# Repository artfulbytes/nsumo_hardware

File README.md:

# Nsumo hardware
This repository contains the schematic and PCB design of Nsumo, a mini-class Sumobot (500g 10x10cm),
created in KiCad, and manufactured by JLCPCB. It's a 2-layer PCB with microcontroller MSP430G2553IPW28,
regulators 3.3V (AMS1117-3.3) and 5V (MP2359), two motor drivers TB6612FNG, IR receiver TSP382, and
circuit protection (RS3E075AT).

## Setup
Import the project into KiCad >6.0 and make sure you have the "default global symbol library table"
and the "default footprint library" available. KiCad should find the 3Dmodels and symbols under _libs/_
automatically. You must manually import the footprints under _libs/footprints/_ (select "file/add library"
from the menu in the footprint editor and add them to the project).

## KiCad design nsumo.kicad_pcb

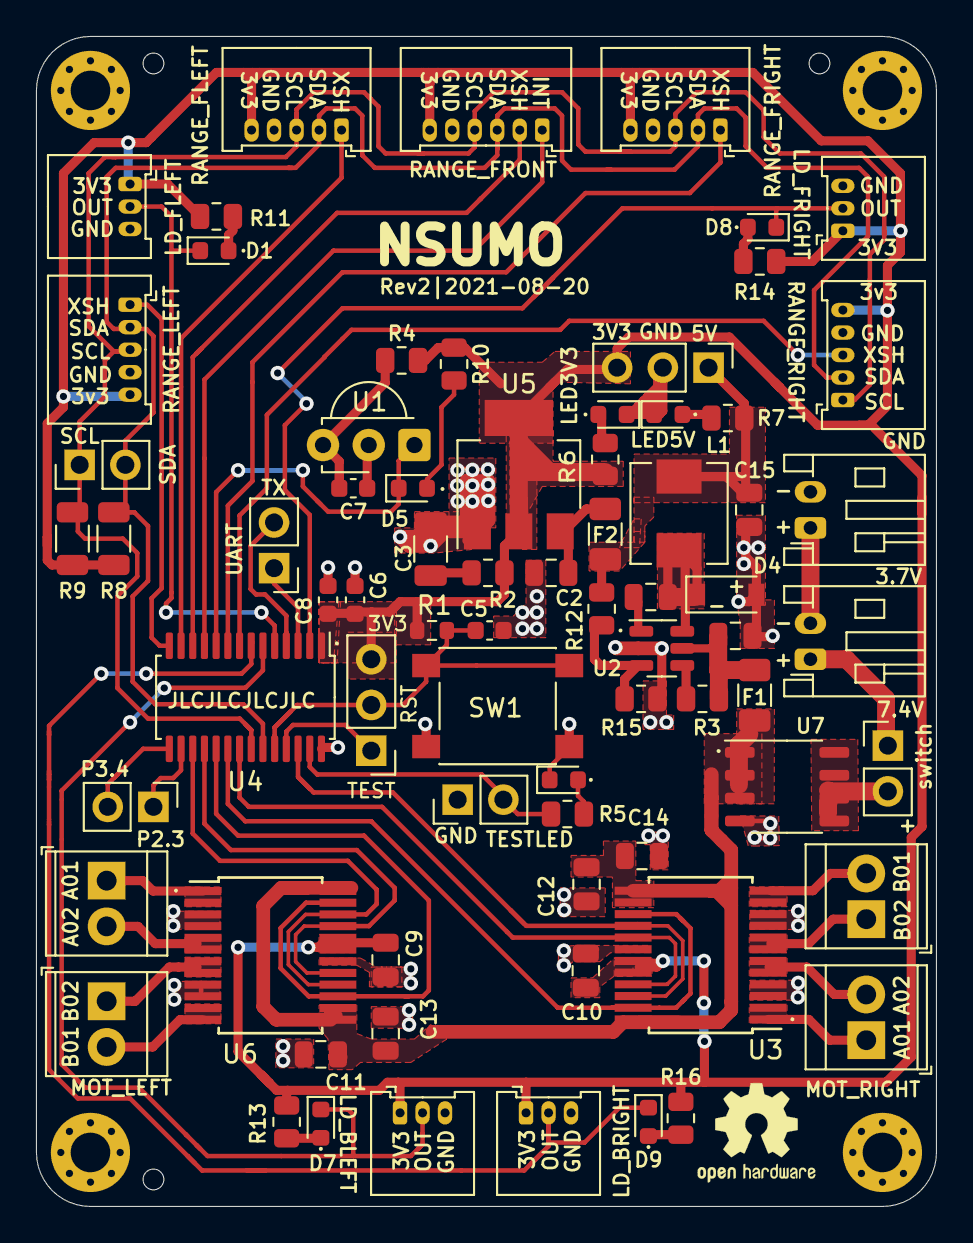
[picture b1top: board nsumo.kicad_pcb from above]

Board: 2 copper layers, 50.0 x 65.0 mm, 77 parts (0 on the bottom side), 57 nets.

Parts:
C1, C13, C14: 10uF; C_0805_2012Metric
C2: 1uF; C_0805_2012Metric
C3: 47uF; C_1206_3216Metric
C4: 10nF; C_0805_2012Metric
C5: 1nF; C_0603_1608Metric
C6: 10uF; C_0603_1608Metric
C7: 1uF; C_0603_1608Metric
C8: 100nF; C_0603_1608Metric
C9, C10, C11, C12: 0.1uF; C_0805_2012Metric
C15: 22uF; C_0805_2012Metric
D1, D5, D7, D8, D9: RED; LED_0603_1608Metric
D2: GREEN; LED_0603_1608Metric
D3: YELLOW; LED_0603_1608Metric
D4: B5819W; D_SOD-123
D6: BLUE; LED_0603_1608Metric
F1, F2: 750mA; Fuse_1206_3216Metric
H1, H2, H3, H4: MountingHole_Pad; MountingHole_2.2mm_M2_Pad_Via
J1: Range_sensor_left; Molex_PicoBlade_53048-0510_1x05_P1.25mm_Horizontal
J2: Range_sensor_front; Molex_PicoBlade_53048-0610_1x06_P1.25mm_Horizontal
J3: BattConn1; JST_PH_S2B-PH-K_1x02_P2.00mm_Horizontal
J4: Range_sensor_front_left; Molex_PicoBlade_53048-0510_1x05_P1.25mm_Horizontal
J5: BattConn0; JST_PH_S2B-PH-K_1x02_P2.00mm_Horizontal
J6: I2C; PinHeader_1x02_P2.54mm_Vertical
J7: Range_sensor_front_right; Molex_PicoBlade_53048-0510_1x05_P1.25mm_Horizontal
J8: UNUSED; PinHeader_1x02_P2.54mm_Vertical
J9: Range_sensor_right; Molex_PicoBlade_53048-0510_1x05_P1.25mm_Horizontal
J10: UART; PinHeader_1x02_P2.54mm_Vertical
J11: SWD; PinHeader_1x03_P2.54mm_Vertical
J12: LED; PinHeader_1x02_P2.54mm_Vertical
J13: PWR; PinHeader_1x03_P2.54mm_Vertical
J14: MOT_FRONT_RIGHT; TerminalBlock_TE_282834-2_1x02_P2.54mm_Horizont
J15: MOT_BACK_RIGHT; TerminalBlock_TE_282834-2_1x02_P2.54mm_Horizont
J16: MOT_FRONT_LEFT; TerminalBlock_TE_282834-2_1x02_P2.54mm_Horizont
J17: MOT_BACK_LEFT; TerminalBlock_TE_282834-2_1x02_P2.54mm_Horizont
J19: Ld_front_left; Molex_PicoBlade_53048-0310_1x03_P1.25mm_Horizontal
J20: Ld_back_left; Molex_PicoBlade_53048-0310_1x03_P1.25mm_Horizontal
J21: Ld_front_right; Molex_PicoBlade_53048-0310_1x03_P1.25mm_Horizontal
J22: Ld_back_right; Molex_PicoBlade_53048-0310_1x03_P1.25mm_Horizontal
L1: 10uH; L_Sunlord_MWSA0518_5.4x5.2mm
R1: 47k; R_0603_1608Metric
R2: 1; R_0805_2012Metric
R3: 100k; R_0805_2012Metric
R4, R5: 470; R_0805_2012Metric
R6, R7: 1k; R_0805_2012Metric
R8, R9: 10k; R_1206_3216Metric
R10, R11, R13, R14, R16: 100; R_0805_2012Metric
R12: 49.9k; R_0805_2012Metric
R15: 9.53k; R_0805_2012Metric
SW1: SW_DPST_x2; SW_Push_1P1T_NO_6x6mm_H9.5mm
SW2: SW_SPST; PinHeader_1x02_P2.54mm_Vertical
U1: TSOP382xx; Vishay_MINICAST-3Pin
U2: MP2359; TSOT-23-6
U3, U6: TB6612FNG; SSOP-24_5.3x8.2mm_P0.65mm_LongPads
U4: MSP430G2553IPW28; TSSOP-28_4.4x9.7mm_P0.65mm
U5: AMS1117-3.3; SOT-223-3_TabPin2
U7: RS3E075AT; SOP-8_3.9x4.9mm_P1.27mm

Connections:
+3V3: C6.1, C8.1, C9.1, C10.1, J1.5, J2.6, J4.5, J7.5, J9.5, J11.3, J13.3, J19.1, J20.1, J21.1, J22.1, R1.2, R2.1, R4.2, R6.1, R8.1, R9.1, R10.1, R11.1, R13.1, R14.1, R16.1, U3.19, U3.20, U4.1, U5.2, U6.19, U6.20
+5V: C15.1, F2.1, J13.1, L1.2, R7.1, R12.1
+BATT: C11.1, C12.1, C13.1, C14.1, F1.1, U3.13, U3.14, U3.24, U6.13, U6.14, U6.24, U7.1, U7.2, U7.3
GND: C1.2, C2.2, C3.2, C5.2, C6.2, C7.2, C8.2, C9.2, C10.2, C11.2, C12.2, C13.2, C14.2, C15.2, D2.1, D3.1, D4.2, D6.1, H1.1, H2.1, H3.1, H4.1, J1.4, J2.5, J4.4, J5.2, J7.4, J9.4, J12.1, J13.2, J19.3, J20.3, J21.3, J22.3, R15.2, SW1.1, U1.2, U2.2, U3.3, U3.4, U3.9, U3.10, U3.18, U4.28, U5.1, U6.3, U6.4, U6.9, U6.10, U6.18, U7.4
INT_FRONT: J2.1, U4.11
IR_RECEIVER: D5.1, U1.1, U4.10
LD_BACK_LEFT: D7.1, J20.2, U4.6
LD_BACK_RIGHT: D9.1, J22.2, U4.7
LD_FRONT_LEFT: D1.1, J19.2, U4.5
LD_FRONT_RIGHT: D8.1, J21.2, U4.2
ML_A01: J17.1, U6.1, U6.2
ML_A02: J17.2, U6.5, U6.6
ML_B01: J16.2, U6.11, U6.12
ML_B02: J16.1, U6.7, U6.8
MOTS_LEFT_CH1: U4.18, U6.17, U6.21
MOTS_LEFT_CH2: U4.17, U6.16, U6.22
MOTS_LEFT_PWM: U4.19, U6.15, U6.23
MOTS_RIGHT_CH1: U3.17, U3.21, U4.21
MOTS_RIGHT_CH2: U3.16, U3.22, U4.26
MOTS_RIGHT_PWM: U3.15, U3.23, U4.20
MR_A01: J15.1, U3.1, U3.2
MR_A02: J15.2, U3.5, U3.6
MR_B01: J14.2, U3.11, U3.12
MR_B02: J14.1, U3.7, U3.8
unnamed: C1.1, F1.2, R3.1, U2.5
unnamed: C2.1, F2.2, U5.3
unnamed: C3.1, R2.2
unnamed: C4.1, U2.1
unnamed: C4.2, D4.1, L1.1, U2.6
unnamed: C7.1, R4.1, U1.3
unnamed: D1.2, R11.2
unnamed: D2.2, R6.2
unnamed: D3.2, R7.2
unnamed: D5.2, R10.2
unnamed: D6.2, R5.2
unnamed: D7.2, R13.2
unnamed: D8.2, R14.2
unnamed: D9.2, R16.2
unnamed: J3.1, SW2.1
unnamed: J3.2, J5.1
unnamed: R3.2, U2.4
unnamed: R12.2, R15.1, U2.3
unnamed: SW2.2, U7.5, U7.6, U7.7, U7.8
RST: C5.1, J11.2, R1.1, SW1.2, U4.24
SBWTCK: J11.1, U4.25
SCL: J1.3, J2.4, J4.3, J6.1, J7.3, J9.1, R9.2, U4.22
SDA: J1.2, J2.3, J4.2, J6.2, J7.2, J9.2, R8.2, U4.23
TEST_LED: J12.2, R5.1, U4.27
UART_RX: J10.1, U4.3
UART_TX: J10.2, U4.4
UNUSED_1: J8.1, U4.16
UNUSED_2: J8.2, U4.15
XSHUT_FLEFT: J4.1, U4.13
XSHUT_FRIGHT: J7.1, U4.9
XSHUT_FRONT: J2.2, U4.12
XSHUT_LEFT: J1.1, U4.14
XSHUT_RIGHT: J9.3, U4.8

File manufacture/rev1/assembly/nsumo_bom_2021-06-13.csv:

Comment,Designator,Footprint,LCSC Part #
"10uF Unpolarized capacitor, small symbol","C6",C_0603_1608Metric,C19702
"10uF Unpolarized capacitor, small symbol","C13,C14,C1",C_0805_2012Metric,C15850
"47uF Unpolarized capacitor, small symbol",C3,C_1206_3216Metric,C96123
"10nF Unpolarized capacitor, small symbol",C4,C_0805_2012Metric,C1710
"1nF Unpolarized capacitor, small symbol",C5,C_0603_1608Metric,C1588
"1uF Unpolarized capacitor, small symbol","C7,C2",C_0805_2012Metric,C28323
"100nF Unpolarized capacitor, small symbol",C8,C_0603_1608Metric,C14663
"0.1uF Unpolarized capacitor, small symbol","C9,C11,C12,C10",C_0805_2012Metric,C49678
GREEN Light emitting diode,"D2,D3",LED_0603_1608Metric,C72043
"B5819W Zener diode, small symbol",D4,D_SOD-123,C8598
RED Light emitting diode,D5,LED_0603_1608Metric,C2286
BLUE Light emitting diode,D6,LED_0603_1608Metric,C72041
"1A Fuse, small symbol",F1,Fuse_0805_2012Metric,
"500mA Fuse, small symbol",F2,Fuse_0805_2012Metric,
MountingHole_Pad Mounting Hole with connection,"H1,H2,H3,H4",MountingHole_2.2mm_M2_Pad_Via,
"Range_sensor_left Generic connector, single row, 01x05, script generated (kicad-library-utils/schlib/autogen/connector/)",J1,Molex_PicoBlade_53048-0510_1x05_P1.25mm_Horizontal,
"UART Generic connector, single row, 01x02, script generated (kicad-library-utils/schlib/autogen/connector/)",J10,PinHeader_1x02_P2.54mm_Vertical,
"Conn_01x03 Generic connector, single row, 01x03, script generated (kicad-library-utils/schlib/autogen/connector/)",J11,PinHeader_1x03_P2.54mm_Vertical,
"MOT_FRONT_RIGHT Generic screw terminal, single row, 01x02, script generated (kicad-library-utils/schlib/autogen/connector/)",J14,TerminalBlock_TE_282834-2_1x02_P2.54mm_Horizont,
"MOT_BACK_RIGHT Generic screw terminal, single row, 01x02, script generated (kicad-library-utils/schlib/autogen/connector/)",J15,TerminalBlock_TE_282834-2_1x02_P2.54mm_Horizont,
"MOT_FRONT_LEFT Generic screw terminal, single row, 01x02, script generated (kicad-library-utils/schlib/autogen/connector/)",J17,TerminalBlock_TE_282834-2_1x02_P2.54mm_Horizont,
"MOT_BACK_LEFT Generic screw terminal, single row, 01x02, script generated (kicad-library-utils/schlib/autogen/connector/)",J18,TerminalBlock_TE_282834-2_1x02_P2.54mm_Horizont,
"Line_detector_front_left Generic connector, single row, 01x03, script generated (kicad-library-utils/schlib/autogen/connector/)",J19,Molex_PicoBlade_53048-0310_1x03_P1.25mm_Horizontal,
"Range_sensor_front Generic connector, single row, 01x06, script generated (kicad-library-utils/schlib/autogen/connector/)",J2,Molex_PicoBlade_53048-0610_1x06_P1.25mm_Horizontal,
"Line_detector_back_left Generic connector, single row, 01x03, script generated (kicad-library-utils/schlib/autogen/connector/)",J20,Molex_PicoBlade_53048-0310_1x03_P1.25mm_Horizontal,
"Line_detector_front_right Generic connector, single row, 01x03, script generated (kicad-library-utils/schlib/autogen/connector/)",J21,Molex_PicoBlade_53048-0310_1x03_P1.25mm_Horizontal,
"Line_detector_back_right Generic connector, single row, 01x03, script generated (kicad-library-utils/schlib/autogen/connector/)",J22,Molex_PicoBlade_53048-0310_1x03_P1.25mm_Horizontal,
"BattConn1 Generic connector, single row, 01x02, script generated (kicad-library-utils/schlib/autogen/connector/)",J3,JST_PH_S2B-PH-K_1x02_P2.00mm_Horizontal,
"Range_sensor_front_left Generic connector, single row, 01x05, script generated (kicad-library-utils/schlib/autogen/connector/)",J4,Molex_PicoBlade_53048-0510_1x05_P1.25mm_Horizontal,
"BattConn0 Generic connector, single row, 01x02, script generated (kicad-library-utils/schlib/autogen/connector/)",J5,JST_PH_S2B-PH-K_1x02_P2.00mm_Horizontal,
"I2C Generic connector, single row, 01x02, script generated (kicad-library-utils/schlib/autogen/connector/)",J6,PinHeader_1x02_P2.54mm_Vertical,
"Range_sensor_front_right Generic connector, single row, 01x05, script generated (kicad-library-utils/schlib/autogen/connector/)",J7,Molex_PicoBlade_53048-0510_1x05_P1.25mm_Horizontal,
"UNUSED Generic connector, single row, 01x02, script generated (kicad-library-utils/schlib/autogen/connector/)","J8,J12",PinHeader_1x02_P2.54mm_Vertical,
"Range_sensor_right Generic connector, single row, 01x05, script generated (kicad-library-utils/schlib/autogen/connector/)",J9,Molex_PicoBlade_53048-0510_1x05_P1.25mm_Horizontal,
"10uH Inductor, small symbol",L1,L_Sunlord_MWSA0518_5.4x5.2mm,C408412
47k Resistor,R1,R_0603_1608Metric,C25819
"0 Resistor, small symbol",R10,R_0805_2012Metric,C17477
"49.9k Resistor, small symbol",R12,R_0805_2012Metric,C17719
"4.7k Resistor, small symbol","R14,R13",R_0805_2012Metric,C17673
"200 Resistor, small symbol",R15,R_0805_2012Metric,C17540
"1 Resistor, small symbol",R2,R_0805_2012Metric,C25271
"100k Resistor, small symbol",R3,R_0805_2012Metric,C17407
1k Resistor,R4,R_0603_1608Metric,C21190
"1k Resistor, small symbol",R6,R_0805_2012Metric,C17513
"470 Resistor, small symbol","R7,R5",R_0805_2012Metric,C17710
"10k Resistor, small symbol","R8,R9",R_1206_3216Metric,C17902
"SW_DPST_x2 Single Pole Single Throw (SPST) switch, separate symbol",SW1,SW_Push_1P1T_NO_6x6mm_H9.5mm,
SW_SPST Single Pole Single Throw (SPST) switch,SW2,PinHeader_1x02_P2.54mm_Vertical,
TestPoint_Probe test point (alternative probe-style design),"TP1,TP2",PinHeader_1x01_P1.00mm_Vertical,
TSOP382xx Photo Modules for PCM Remote Control Systems,U1,Vishay_MINICAST-3Pin,C141632
MP2359 ,U2,TSOT-23-6,C14259
"TB6612FNG Driver IC for Dual DC motor, SSOP-24","U3,U6",SSOP-24_5.3x8.2mm_P0.65mm,
"MSP430G2553IPW28 1kB Flash, 256B RAM, TSSOP-28",U4,TSSOP-28_4.4x9.7mm_P0.65mm,
"AMS1117-3.3 1A Low Dropout regulator, positive, 1.5V fixed output, SOT-223",U5,SOT-223-3_TabPin2,C6186
AO4411 ,U7,SOIC-8_3.9x4.9mm_P1.27mm,C19234

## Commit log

2021-06-13 NEW: Add files for the first time
    Only stored the files locally until now...
2021-06-15 FIX: Change PTC fuse footprint from 0805 to 1206
    There are more ones available in 1206 at Digi-Key.
2021-07-17 FIX: Add missing datasheets to BOM
2022-04-03 ENH: REV2
    First revision had several issues. Fix these for
    revision 2.
2022-04-03 README
2022-04-03 NEW: REV2 files
2022-04-03 NEW: README nsumo preview
2022-04-03 FIX: Small updates to README
2022-04-03 Move revision files
2022-04-03 FIX: Add some more info to README
2022-04-23 ENH: Update the project for KiCad 6.0
    Make the project compatible with KiCad 6.0 and add some notes
    about importing it.
2022-06-28 FIX: Add missing 3D models
    * Button switch
    * Inductor
    * Mosfet
    * Motor drivers
